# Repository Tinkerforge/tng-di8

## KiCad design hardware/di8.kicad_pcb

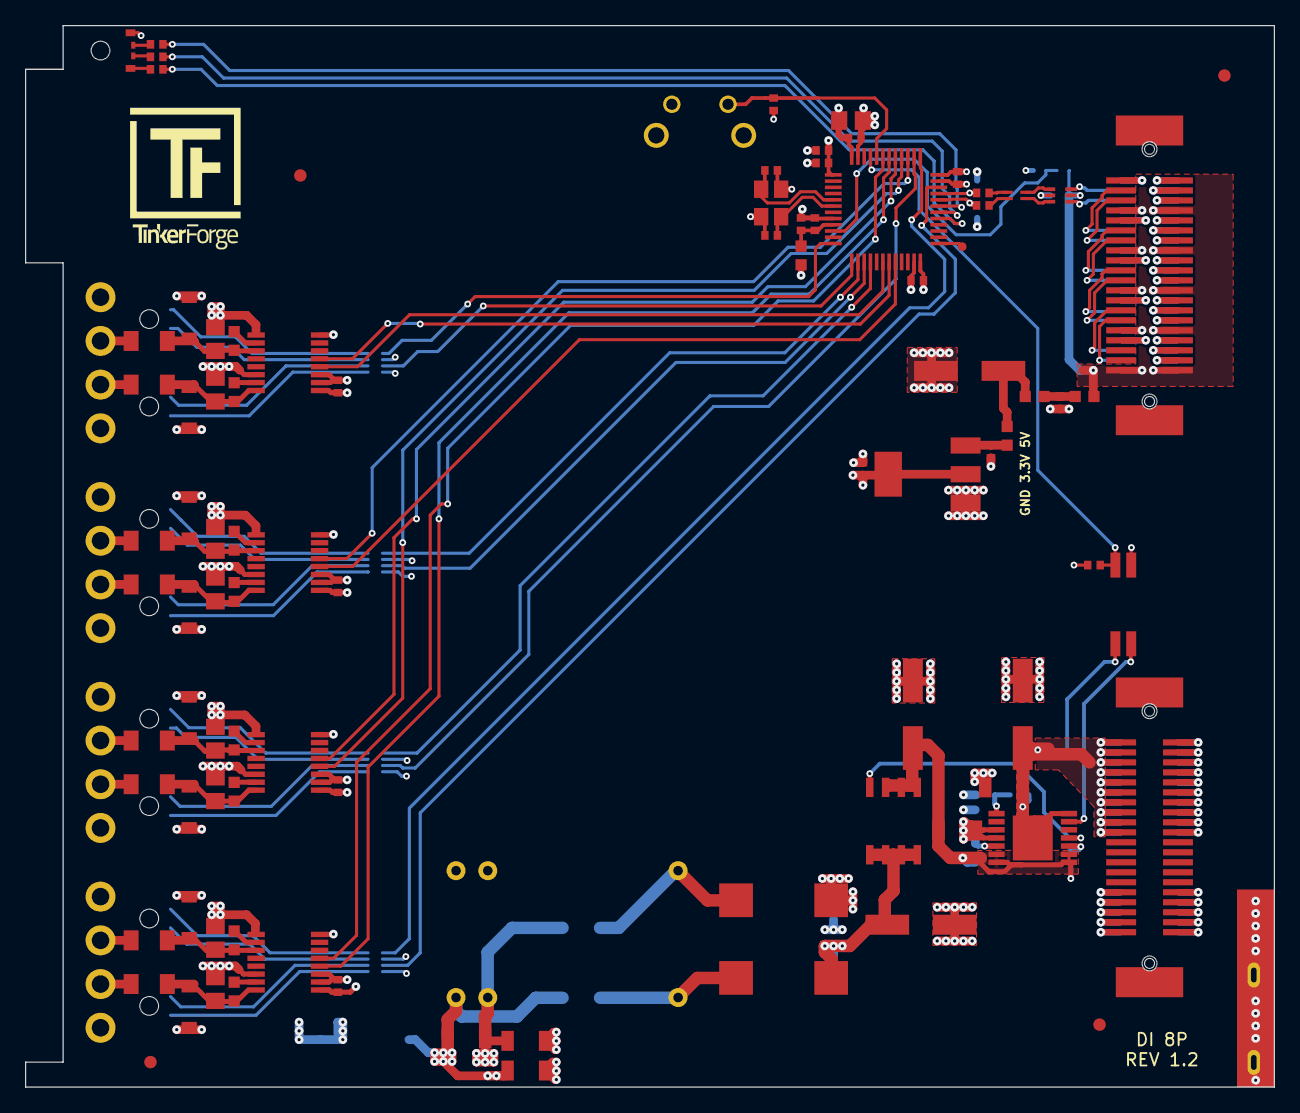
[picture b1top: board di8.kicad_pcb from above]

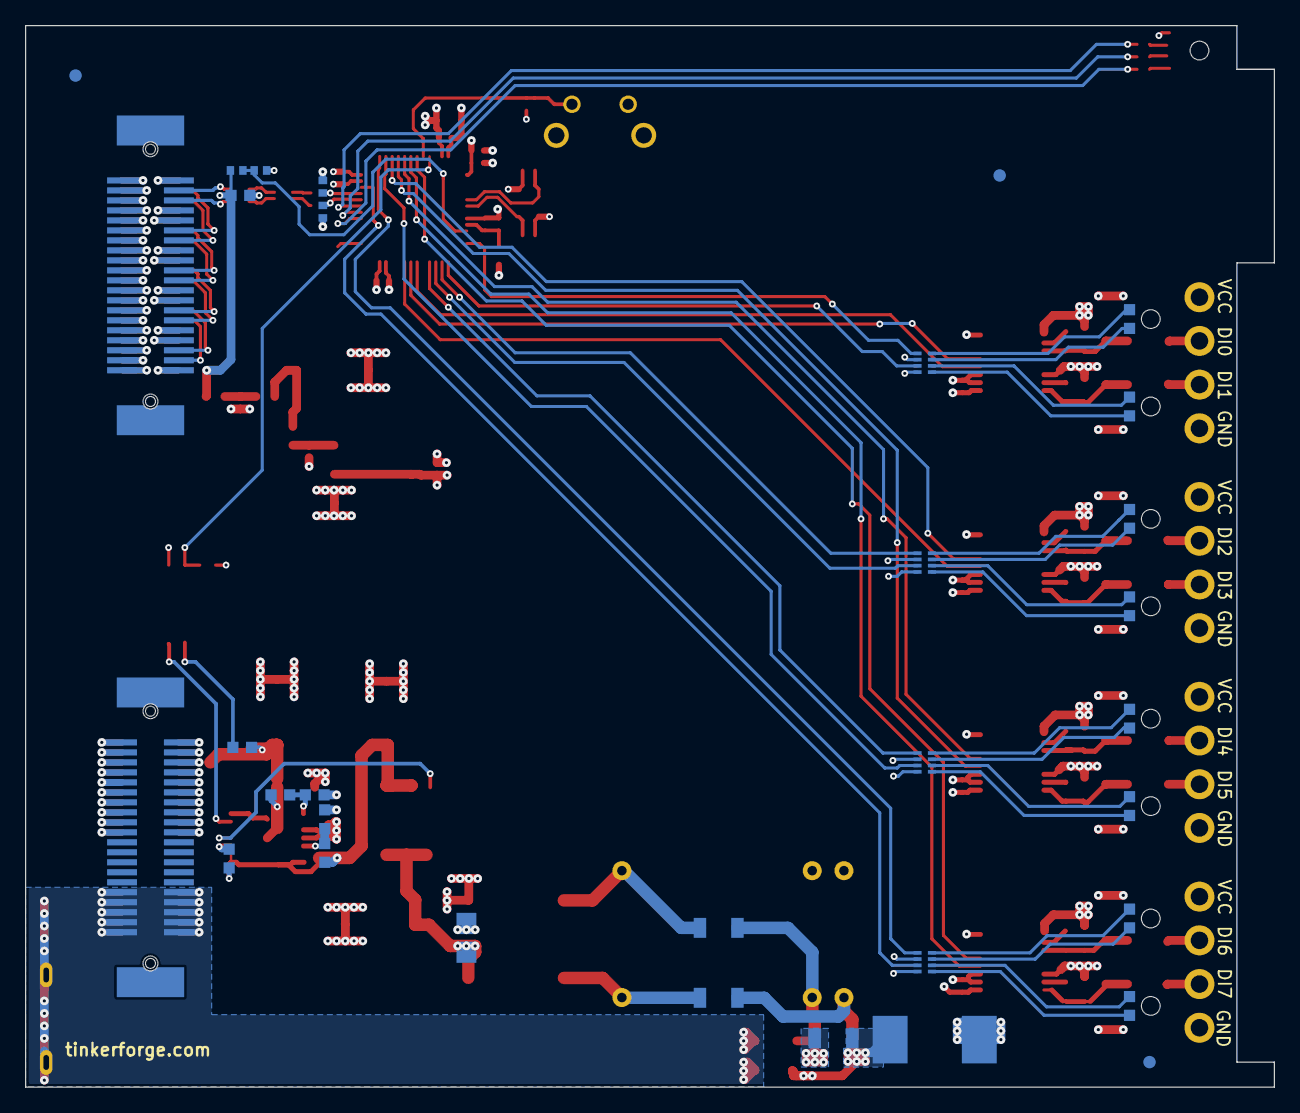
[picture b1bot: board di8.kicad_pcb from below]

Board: 4 copper layers, 100.0 x 85.0 mm, 130 parts (33 on the bottom side), 106 nets.

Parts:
C101, C102, C116, C117: 1uF; C0402F
C103, C104, C105, C106, C107, C112, C204, C211, C212, C213: 100nF; C0402F
C108, C109: 33pF; C0402F
C110: 10uF; C0805E
C111: 100uF; ELKO_63
C113, C114: 47pF; C0402F
C115: 2.2uF; C0603F
C118: 10uF/50V; C1206
C119, C120: 0; C1206
C121, C125, C126: 10uF/35V; C1206
C122, C123, C124: 100uF/35V; ELKO_63
C127, C128: 1nF/2kV; C1206
C202, C203, C205, C206, C207, C208, C209, C210: DNP; C0805E
D101: 3.0SMI30CATR; SMC
D201, D202, D211, D212, D213, D214, D215, D216: SMF36CA; SOD-123FL
D203, D204, D205, D206, D207, D208, D209, D210: LED; LED-LP
Fiducial_Mark: VAL**; Fiducial_Mark
Fiducial_Mark#2, Fiducial_Mark#3, Fiducial_Mark#4, Fiducial_Mark#5, Fiducial_Mark#6, Fiducial_Mark#7: VAL**; Fiducial_Mark
J101: TNG-Power-TOP; TNG-40-TOP
J102: TNG-Power-BTM; TNG-40-BTM
J103: TNG-Data-TOP; TNG-40-TOP
J104: TNG-Data-BTM; TNG-40-BTM
L101: FB; R0603F
L102, L103, L104: INDUCTs; R0603F
L105: 744230900; WE-CNSW-0603
LED101: EASV3015RGBA0; LED-RGB-LP
P102: Debug; DEBUG_PAD
P103: PE; PE_Hook
P201: INPUT0; OQ_4P
P202: INPUT1; OQ_4P
P203: INPUT2; OQ_4P
P204: INPUT3; OQ_4P
Q101: FDS8449; SOIC-8-MOSFET
R101, R107, R108: 1k; R0402F
R102, R105: 0; R0402F
R103, R104: 22; R0402F
R106: 56; R0402F
R109: 10k; R0402F
R110, R115: 10k; R0603F
R111, R112: DNP; R0603F
R113: 22; R0603F
R114: 68k; R0603F
R116: VC1206K201R030; R1206
R201, R202, R205, R206, R207, R208, R209, R210: 1k; RMELF
R203, R204, R211, R212, R213, R214, R215, R216: 562; R0603F
RP201, RP202, RP203, RP204: 470; 4X0402
SW101: BOOT; TACT-6MM-HOR
T101: 744273222; WE-SL5
U101: STM32F070CBT6; LQFP48
U102: AZ1117EH; SOT-223
U103: 82400152; SOT563-SPEC
U104: DNP; TEL10
U105: TLP293; SOP4
U106: STEF01; HTSSOP14
U201, U202, U203, U204: ISO1212; SSOP16
X101: 8MHz; CRYSTAL_3225

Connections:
3V3: C101.1, C103.1, C104.1, C105.1, C106.1, C110.1, C116.1, C204.2, C211.2, C212.2, C213.2, L101.1, LED101.1, R109.2, RP201.2, RP201.4, RP202.2, RP202.4, RP203.2, RP203.4, RP204.2, RP204.4, SW101.1, U101.1, U101.24, U101.36, U101.48, U102.2, U201.2, U201.3, U202.2, U202.3, U203.2, U203.3, U204.2, U204.3
5VA: C115.1, J103.7, J103.8, J103.15, J103.16, J103.23, J103.24, J103.31, J103.32, J103.39, J103.40, J104.7, J104.8, J104.15, J104.16, J104.23, J104.24, J104.31, J104.32, J104.39, J104.40, L104.1, R107.1, U103.5
+5V: C111.1, L102.1, L103.2
AGND: C118.2, C120.1, C128.2, C202.1, C203.1, C205.1, C206.1, C207.1, C208.1, C209.1, C210.1, D101.2, D201.2, D202.2, D211.2, D212.2, D213.2, D214.2, D215.2, D216.2, P201.4, P202.4, P203.4, P204.4, R116.2, U104.10, U201.9, U201.14, U202.9, U202.14, U203.9, U203.14, U204.9, U204.14
AGNDA: C121.2, C122.2, C123.2, C124.2, C125.2, C126.2, J101.2, J101.4, J101.6, J101.8, J101.10, J101.12, J101.14, J101.16, J101.18, J101.20, J102.1, J102.3, J102.5, J102.7, J102.9, J102.11, J102.13, J102.15, J102.17, J102.19, R112.2, R115.2, T101.2, U106.3, U106.4
AIN0: R107.2, R108.1, U101.10
Earth: C127.2, C128.1, J101.31, J101.32, J101.33, J101.34, J101.35, J101.36, J101.37, J101.38, J101.39, J101.40, J102.31, J102.32, J102.33, J102.34, J102.35, J102.36, J102.37, J102.38, J102.39, J102.40, P103.1
GND: C101.2, C102.2, C103.2, C104.2, C105.2, C106.2, C107.2, C108.1, C109.1, C110.2, C111.2, C112.2, C113.2, C114.2, C115.2, C116.2, C117.2, C204.1, C211.1, C212.1, C213.1, J103.1, J103.2, J103.4, J103.6, J103.9, J103.10, J103.12, J103.14, J103.17, J103.18, J103.20, J103.22, J103.25, J103.26, J103.28, J103.30, J103.33, J103.34, J103.36, J103.38, J104.1, J104.2, J104.3, J104.5, J104.9, J104.10, J104.11, J104.13, J104.17, J104.18, J104.19, J104.21, J104.25, J104.26, J104.27, J104.29, J104.33, J104.34, J104.35, J104.37, R101.1, R108.2, U101.8, U101.23, U101.35, U101.47, U102.1, U103.2, U105.3, U201.1, U201.8, U202.1, U202.8, U203.1, U203.8, U204.1, U204.8, X101.3
IN0: U101.18, U201.4
IN1: U101.19, U201.5
IN2: U101.20, U202.4
IN3: U101.39, U202.5
IN4: U101.40, U203.4
IN5: U101.41, U203.5
IN6: U101.42, U204.4
IN7: U101.43, U204.5
LED0: RP201.1, U101.12
LED1: RP201.3, U101.13
LED2: RP202.1, U101.14
LED3: RP202.3, U101.15
LED4: RP203.1, U101.16
LED5: RP203.3, U101.38
LED6: RP204.1, U101.37
LED7: RP204.3, U101.34
LEDB: R106.1, U101.31
LEDG: R105.1, U101.30
LEDR: R102.1, U101.29
unnamed: C102.1, C107.1, L101.2, U101.9
unnamed: C108.2, U101.5, X101.2
unnamed: C109.2, U101.6, X101.1
unnamed: C112.1, L103.1, L104.2
unnamed: C117.1, L102.2, U102.3
unnamed: C119.2, T101.4, U104.16
unnamed: C120.2, T101.3, U104.1
unnamed: C121.1, C123.1, Q101.D, T101.1
unnamed: C202.2, D202.1, R201.1, R203.2, U201.16
unnamed: C203.2, D201.1, R202.1, R204.2, U201.11
unnamed: C205.2, D214.1, R205.1, R211.2, U202.16
unnamed: C206.2, D211.1, R206.1, R212.2, U202.11
unnamed: C207.2, D215.1, R207.1, R213.2, U203.16
unnamed: C208.2, D212.1, R208.1, R214.2, U203.11
unnamed: C209.2, D216.1, R209.1, R215.2, U204.16
unnamed: C210.2, D213.1, R210.1, R216.2, U204.11
unnamed: D203.1, RP201.7
unnamed: D203.2, RP201.8
unnamed: D204.1, RP201.5
unnamed: D204.2, RP201.6
unnamed: D205.1, RP202.7
unnamed: D205.2, RP202.8
unnamed: D206.1, RP202.5
unnamed: D206.2, RP202.6
unnamed: D207.1, RP203.7
unnamed: D207.2, RP203.8
unnamed: D208.1, RP203.5
unnamed: D208.2, RP203.6
unnamed: D209.1, RP204.7
unnamed: D209.2, RP204.8
unnamed: D210.1, RP204.5
unnamed: D210.2, RP204.6
unnamed: J103.3, J104.12
unnamed: J103.5, J104.14
unnamed: J103.11, J104.20
unnamed: J103.13, J104.22
unnamed: J103.19, J104.28
unnamed: J103.21, J104.30
unnamed: J103.27, J104.36
unnamed: J103.29, J104.38
unnamed: LED101.2, R106.2
unnamed: LED101.3, R105.2
unnamed: LED101.4, R102.2
unnamed: P102.1, U101.25
unnamed: P201.2, R202.2
unnamed: P201.3, R201.2
unnamed: P202.2, R206.2
unnamed: P202.3, R205.2
unnamed: P203.2, R208.2
unnamed: P203.3, R207.2
unnamed: P204.2, R210.2
unnamed: P204.3, R209.2
unnamed: Q101.G, U106.11
unnamed: R101.2, SW101.2, U101.44
unnamed: R110.2, U105.1
unnamed: R111.2, R112.1, U106.5
unnamed: R113.2, U106.10
unnamed: R114.2, R115.1, U106.1
unnamed: R203.1, U201.15
unnamed: R204.1, U201.10
unnamed: R211.1, U202.15
unnamed: R212.1, U202.10
unnamed: R213.1, U203.15
unnamed: R214.1, U203.10
unnamed: R215.1, U204.15
unnamed: R216.1, U204.10
PWR_GOOD: R109.1, U101.45, U105.4
PWR_PG: U105.2, U106.13
USB-DM: C114.1, R104.2, U101.32
USB-DMA: J104.6, U103.4
USB-DMB: L105.1, U103.3
USB-DMC: L105.2, R104.1
USB-DP: C113.1, R103.2, U101.33
USB-DPA: J104.4, U103.6
USB-DPB: L105.4, U103.1
USB-DPC: L105.3, R103.1
VCC: C118.1, C119.1, C127.1, D101.1, P201.1, P202.1, P203.1, P204.1, R116.1, U104.9
VCCPWRA: C122.1, C126.1, J101.1, J101.3, J101.5, J101.7, J101.9, J101.11, J101.13, J101.15, J101.17, J101.19, J102.2, J102.4, J102.6, J102.8, J102.10, J102.12, J102.14, J102.16, J102.18, J102.20, R110.1, R114.1, U106.14, U106.EXP
VO: C124.1, C125.1, Q101.S, R111.1, R113.1, U106.6, U106.7, U106.8, U106.9

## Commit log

2019-06-07 Add first working blinkenlights for new TNG module
    This uses initial integration into bricklib
2019-06-07 Move system timer initialization to bricklib
2019-06-07 Add tests for coop task and logging support
2019-06-18 Add TNG-DI8 communication test
2019-06-19 start hardware design, schematic nearly finished
2019-06-19 Add compatability for bootloader in front of firmware
2019-06-25 Use specifically generated usb firmware for USB flashing
2019-06-25 Add crc32.c and tng_firmware.c to makefile for flashing support
2019-07-01 add first parts to pcb
2019-07-09 partial placement
2019-07-24 add dc dc converter, routing
2019-07-24 more routing
2019-07-25 routing completed
2019-07-25 routing improvement, ordered version 1.0
2019-08-20 Change processor to STM32F070xB
2019-08-20 Implement test di8 driver
2019-08-22 Add examples
2019-08-26 add hints
2019-08-26 add another hint
2019-10-02 add input protection (not finished)
2019-10-16 version 1.1 fully routed
2019-10-18 specify tvs diodes, add fiducials
2019-11-08 cutout for rgb led added
2019-11-20 add boot switch
2019-11-22 improve lightpipes
2019-11-22 add vcc input protection
2019-11-28 outline update
2019-12-10 fix name
2019-12-23 update rgb led drill diameter
2019-12-30 fix inductor footprints
2020-01-02 add stuff
2020-01-14 examples: Use python3 input by default.
2020-03-02 add hook footprint
2020-05-13 Add initial tests
2020-05-14 fix values
2020-05-14 fix value
2020-07-20 Implement initial simplified API
2020-07-27 Use HAL Config from bricklib2
2020-07-27 Add TIM defines for status LEDs
2020-08-25 examples: Adapt to API changes
2020-09-04 add version 1.2
    fix footprints
2020-09-07 specify capactors
2020-09-07 fix stuff
2020-09-08 all footprints updated
2020-09-09 default is non implemented
2020-09-10 fix 3d stuff
2022-04-27 mathematica: Call getter only once

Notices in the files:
hardware/di8.kicad_pcb:
Licensed under CERN OHL v.1.1
Copyright (©) 2020, B.Nordmeyer
Copyright Tinkerforge GmbH 2020.
This documentation describes Open Hardware and is licensed under the
CERN OHL v. 1.1.
